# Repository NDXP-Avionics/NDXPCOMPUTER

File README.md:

# NDXP COMPUTER!!!!!!

## Contributing
This repository is open at all times to any member submitting a Pull Request and merging their code directly into the main branch after approval! If you don't know what a Pull Request is, or if this is your first time using github, it is recommended that you watch [this](https://docs.github.com/en/get-started/start-your-journey/hello-world) guide before you begin.

### Requirements
Before you do anything, make sure you:
 - Have [git](https://git-scm.com/downloads) installed on your computer (macos should by default).
 - Have [kicad](https://www.kicad.org/) installed on your computer
 - Are added as a repository contributor (ask a team lead)

To make a contribution, the generall process is:

<b><i>clone/pull → branch → make your changes → add;commit;push → request approval for merge</i></b>

Each step is broken down as follows:

### Clone/Pull 🤖
If this is your first time interacting with this repository on your local machine, execute the following command in the location on your computer you wish to clone the repository to:

```
git clone https://github.com/NDXP-Avionics/NDXPCOMPUTER
```

If you have the repository already and wish to begin a new contribution <b><u>it is important that you get the most recent version of the repository: </u></b>

```
git switch master
git pull origin master --rebase
```

### Branch 🪾
Once you have an up to date copy of the repository on your local machine, you will need to create a new branch for your contribution:

```
git branch -c branch-name
```

```
git switch branch-name
```

Feel free to name it whatever you want. Be descriptive!

### Make Your Changes 👨‍💻
At this point, you are free to make whatever changes you want! Any time you are working in your local copy, you do not have to worry about messing up the project. Feel free to delete the entire thing if you want!
 - Experiment
 - Break Things
 - Absolutely Cook 👨‍🍳

<b>THIS IS HOW WE LEARN!!</b>

### Add;Commit;Push 💡
When you are satisfied with your contribution, execute the following steps to push your changes to github for review:

```
git add .
```

```
git commit -m "your-descriptive-message"
```

```
git push origin branch-name
```

Once that is done, your code should be pushed to this repository! The final step is to submit a pull request for your code to the main branch using this website, and it will be reviewed for merge shortly!

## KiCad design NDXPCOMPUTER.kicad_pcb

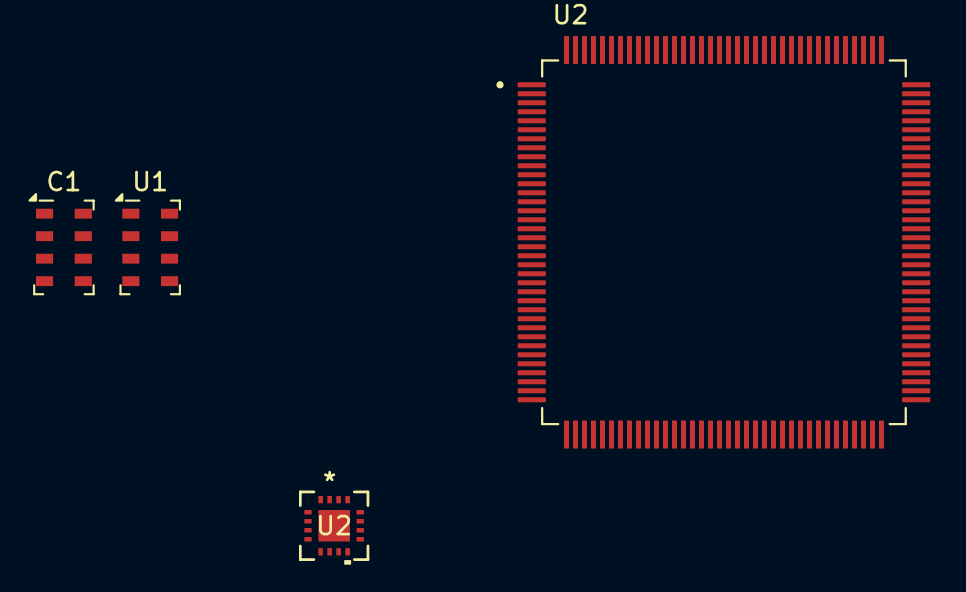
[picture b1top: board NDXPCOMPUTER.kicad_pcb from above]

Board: 2 copper layers, 4 parts (0 on the bottom side), 5 nets, no tracks yet.

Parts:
C1: 100nf; LGA-8_3x5mm_P1.25mm
U1: MS5611-01BA; LGA-8_3x5mm_P1.25mm
U2: TS30013-M033QFNR; QFN16_3X3_SEM
U2#2: STM32H743ZIT6; QFP50P2200X2200X160-144N

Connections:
+3V3: C1.1, U1.1 (VDD), U1.2 (PS)
GND: C1.2, U1.3 (GND), U1.4 (CSB), U1.5 (CSB)
VCAP: U2#2.71 (VCAP), U2#2.106 (VCAP)
VDD: U2#2.17 (VDD), U2#2.30 (VDD), U2#2.39 (VDD), U2#2.52 (VDD), U2#2.62 (VDD), U2#2.72 (VDD), U2#2.84 (VDD), U2#2.108 (VDD), U2#2.121 (VDD), U2#2.131 (VDD), U2#2.144 (VDD)
VSS: U2#2.16 (VSS), U2#2.38 (VSS), U2#2.51 (VSS), U2#2.61 (VSS), U2#2.83 (VSS), U2#2.94 (VSS), U2#2.107 (VSS), U2#2.120 (VSS), U2#2.130 (VSS)
